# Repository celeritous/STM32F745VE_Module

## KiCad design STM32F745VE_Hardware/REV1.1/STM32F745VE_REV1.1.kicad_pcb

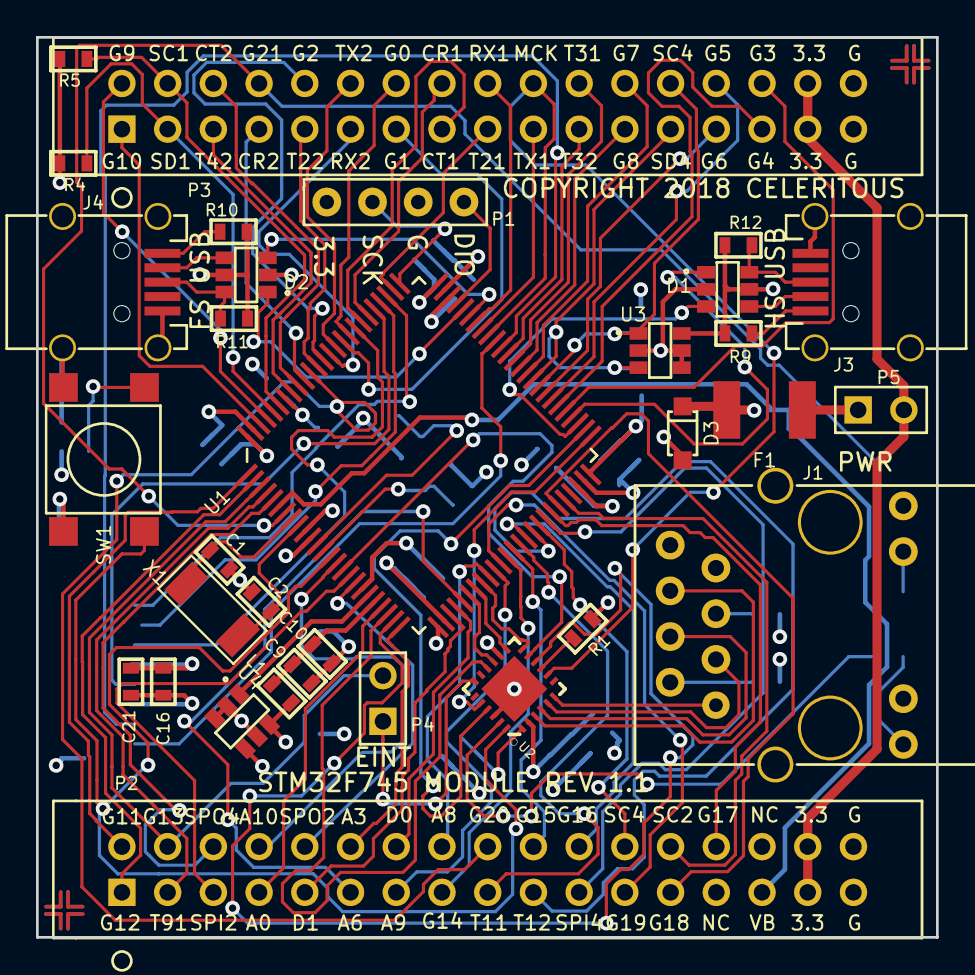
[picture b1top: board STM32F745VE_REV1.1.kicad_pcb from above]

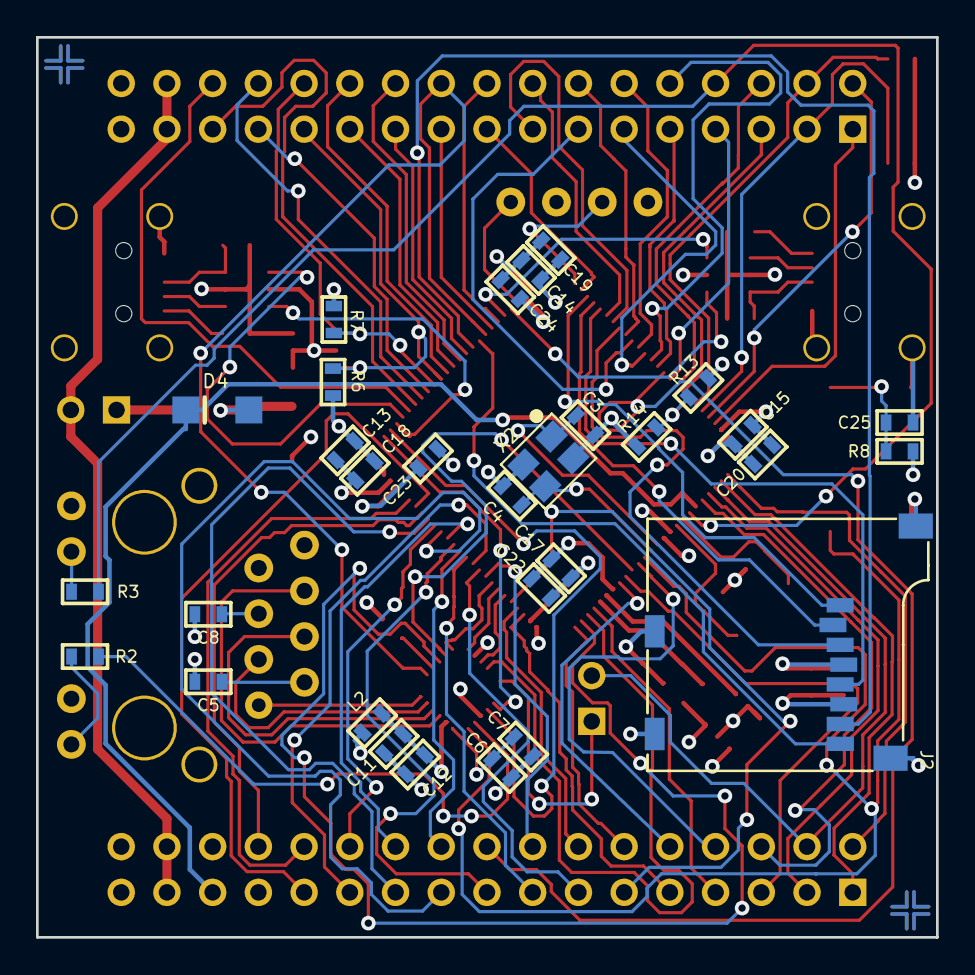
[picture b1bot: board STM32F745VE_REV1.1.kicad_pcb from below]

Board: 4 copper layers, 50.0 x 50.0 mm, 66 parts (30 on the bottom side), 112 nets.

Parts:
C1, C2, C3, C4: 12pF; P0603
C5, C6, C8, C9, C11, C13, C14, C15, C16, C17: 0.10uF; P0603
C7, C23, C24: 2.2uF; P0603
C10, C12, C18, C19, C20, C21, C22: 10.0uF; P0603
C25: 0.010uF; P0603
D1, D2: USBLC6-2; SOT23-6
D3: SMP3V3; SOD123
D4: D_Small; MINI_SMA
F1: FUSE_PTC_.75A_33V; P1812
J1: CONNECTOR_RJ45_SI-60062; CONNECTOR_ETHERNET_SI60062
J2: SOCKET_MICRO_SD_SMT_3M; CONN_SDMICRO_3M
J3, J4: USB_MINI_B_SMD; CONN_USB_UX60-MB
L1, L2: FERRITE_BEAD; P0603
P1: CONN_1x4; Connector_1x4_100mil_TH
P2, P3: Header_2x17; Header_2x17_Shrouded_100mil
P4, P5: Header_2x1; Header_2x1_Shrouded_100mil
R1: 6.49kΩ; P0603
R2, R3: 220.0Ω; P0603
R4, R5, R6, R7, R8, R14: 4.70kΩ; P0603
R9, R10, R13: ZERO_Ω; P0603
R11, R12: 1.50kΩ; P0603
REF01, REF04: FIDUCIAL_BOTTOM
REF02, REF03: FIDUCIAL_TOP
SW1: PUSHBUTTON_SPST_6MM_SMD; SWITCH_6MM_PB
U1: STM32F745VE; QFP_100_14X14_0.5
U2: KSZ8081RNA; QFN24_4X4mm_0.5mm_PWR
U3: 24AA02E64OT; SOT23-6
U4: MCP1501-30; SOT23-6
X1: ABS10-32.768kHz; XTAL_1.8X4.9mm
X2: ABM8G-12.00MHz; XTAL_3.2X2.5

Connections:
+3.3V: C13.1, C14.1, C15.1, C16.1, C17.1, C18.1, C19.1, C20.1, C21.1, C22.1, D1.5, D2.5, D3.K, D4.A, F1.1, J1.10, J1.12, J2.4, L1.1, L2.1, P1.4, R4.2, R5.2, R6.2, R7.2, R8.1, R9.1, R10.1, R11.1, R12.2, R13.1, U1.11, U1.27, U1.50, U1.75, U1.100, U2.14, U3.6, U4.4, U4.6
/+3.0VREF: U1.20, U4.1
/+3.3VANA: C9.1, C10.1, L1.2, U1.21
/+3.3VETH: C11.1, C12.1, L2.2, U2.2
/+3.3VEXT: P2.31, P2.32, P3.31, P3.32, P5.2
/ADC_0: P2.7, U1.22
/ADC_3: P2.12, U1.25
/ADC_6: P2.11, U1.30
/ADC_8: P2.16, U1.34
/ADC_9: P2.13, U1.35
/ADC_10: P2.8, U1.15
/BOOT0: R13.2, R14.1, U1.94
/CAN1_RX: P3.16, U1.81
/CAN1_TX: P3.15, U1.82
/CAN2_RX: P3.7, U1.91
/CAN2_TX: P3.6, U1.92
/DAC_0: P2.14, U1.29
/DAC_1: P2.9, U1.28
/ETH_CRS_DV: U1.31, U2.15
/ETH_INT: P4.1, U2.18
/ETH_LED: R2.1, U2.23
/ETH_MDC: U1.16, U2.11
/ETH_MDIO: U1.24, U2.10
/ETH_REF_CLK: U1.23, U2.16
/ETH_RXC: C8.1, J1.5
/ETH_RXD0: U1.32, U2.13
/ETH_RXD1: U1.33, U2.12
/ETH_RXM: J1.6, U2.3
/ETH_RXP: J1.4, U2.4
/ETH_TXC: C5.1, J1.2
/ETH_TXD0: U1.51, U2.20
/ETH_TXD1: U1.52, U2.21
/ETH_TXM: J1.3, U2.5
/ETH_TXP: J1.1, U2.6
/GPIO_0: P3.14, U1.84
/GPIO_1: P3.13, U1.85
/GPIO_2: P3.10, U1.88
/GPIO_3: P3.30, U1.55
/GPIO_4: P3.29, U1.56
/GPIO_5: P3.28, U1.57
/GPIO_6: P3.27, U1.58
/GPIO_7: P3.24, U1.61
/GPIO_8: P3.23, U1.62
/GPIO_9: P3.2, U1.97
/GPIO_10: P3.1, U1.98
/GPIO_11: P2.2, U1.1
/GPIO_12: P2.1, U1.2
/GPIO_13: P2.4, P4.2, U1.3
/GPIO_14: P2.15, U1.37
/GPIO_15: P2.20, U1.38
/GPIO_16: P2.22, U1.40
/GPIO_17: P2.28, U1.44
/GPIO_18: P2.25, U1.45
/GPIO_19: P2.23, U1.36
/GPIO_20: P2.18, U1.90
/GPIO_21: P3.8, R3.1, U1.7
/I2C1_SCL: P3.4, R5.1, U1.95
/I2C1_SDA: P3.3, R4.1, U1.96
/I2C4_SCL: P3.26, R7.1, U1.59, U3.1
/I2C4_SDA: P3.25, R6.1, U1.60, U3.3
/JTAG_SWCLK: P1.3, U1.76
/JTAG_SWDIO: P1.1, U1.72
/MCLKOUT: P3.20, U1.67, U2.8
/MCU_RST: SW1.2, U1.14, U2.24
/OSC32IN: C1.1, U1.8, X1.1
/OSC32OUT: C2.1, U1.9, X1.2
/OSCHSIN: C3.1, U1.12, X2.1
/OSCHSOUT: C4.1, U1.13, X2.3
/SDMMC_CK: J2.5, U1.80
/SDMMC_CMD: J2.3, U1.83
/SDMMC_D0: J2.7, U1.65
/SDMMC_D1: J2.8, U1.66
/SDMMC_D2: J2.1, U1.78
/SDMMC_D3: J2.2, U1.79
/SPI2_MISO: P2.5, U1.17
/SPI2_MOSI: P2.10, U1.18
/SPI2_SCK: P2.26, U1.46
/SPI4_MISO: P2.21, U1.43
/SPI4_MOSI: P2.6, U1.5
/SPI4_SCK: P2.24, U1.42
/TIM1_CH1: P2.17, U1.39
/TIM1_CH2: P2.19, U1.41
/TIM2_CH1: P3.17, U1.77
/TIM2_CH2: P3.9, U1.89
/TIM3_CH1: P3.22, U1.63
/TIM3_CH2: P3.21, U1.64
/TIM4_CH2: P3.5, U1.93
/TIM9_CH1: P2.3, U1.4
/USART1_RX: P3.18, U1.69
/USART1_TX: P3.19, U1.68
/USART2_RX: P3.11, U1.87
/USART2_TX: P3.12, U1.86
/USB_FS_DM: D2.3, U1.70
/USB_FS_DP: D2.1, U1.71
/USB_HS_DM: D1.3, U1.53
/USB_HS_DP: D1.1, U1.54
/VBATT: D4.K, P2.29, U1.6
/VCAP1: C23.1, U1.48
/VCAP2: C24.1, U1.73
GND: C1.2, C2.2, C3.2, C4.2, C5.2, C6.2, C7.2, C8.2, C9.2, C10.2, C11.2, C12.2, C13.2, C14.2, C15.2, C16.2, C17.2, C18.2, C19.2, C20.2, C21.2, C22.2, C23.2, C24.2, C25.2, D1.2, D2.2, D3.A, J1.8, J2.6, J2.9, J2.10, J2.11, J2.12, J3.5, J3.6, J3.7, J3.8, J3.9, J4.5, J4.6, J4.7, J4.8, J4.9, P1.2, P2.33, P2.34, P3.33, P3.34, R1.1, R14.2, SW1.3, SW1.4, U1.10, U1.19, U1.26, U1.49, U1.74, U1.99, U2.22, U2.25, U3.2, U3.4, U3.5, U4.2, U4.3, U4.5, X2.2, X2.4
unnamed: C6.1, C7.1, U2.1
unnamed: C25.1, R8.2, SW1.1
unnamed: D1.4, J3.2
unnamed: D1.6, J3.3, R12.1
unnamed: D2.4, J4.2
unnamed: D2.6, J4.3, R11.2
unnamed: F1.2, P5.1
unnamed: J1.9, R2.2
unnamed: J1.11, R3.2
unnamed: J3.1, R9.2
unnamed: J4.1, R10.2
unnamed: R1.2, U2.9

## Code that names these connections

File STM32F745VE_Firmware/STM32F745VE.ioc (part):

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Mcu.Name=STM32F745V(E-G)Tx
Mcu.Package=LQFP100
Mcu.UserName=STM32F745VETx
PA0/WKUP.Signal=ADCx_IN0
PA1.Mode=RMII
PA1.Signal=ETH_REF_CLK
PA10.Mode=Asynchronous
PA10.Signal=USART1_RX
PA11.Mode=Device_Only
PA11.Signal=USB_OTG_FS_DM
PA12.Mode=Device_Only
PA12.Signal=USB_OTG_FS_DP
PA13.Mode=Serial_Wire
PA13.Signal=SYS_JTMS-SWDIO
PA14.Mode=Serial_Wire
PA14.Signal=SYS_JTCK-SWCLK
PA15.Signal=S_TIM2_CH1_ETR
PA2.Mode=RMII
PA2.Signal=ETH_MDIO
PA3.Signal=ADCx_IN3
PA4.Signal=COMP_DAC1_group
PA5.Signal=COMP_DAC2_group
PA6.Signal=ADCx_IN6
PA7.Mode=RMII
PA7.Signal=ETH_CRS_DV
PA8.Mode=Clock-out-1
PA8.Signal=RCC_MCO_1
PA9.Mode=Asynchronous
PA9.Signal=USART1_TX
PB0.Signal=ADCx_IN8
PB1.Signal=ADCx_IN9
PB10.Mode=Full_Duplex_Master
PB10.Signal=SPI2_SCK
PB11.Mode=RMII
PB11.Signal=ETH_TX_EN
PB12.Mode=RMII
PB12.Signal=ETH_TXD0
PB13.Mode=RMII
PB13.Signal=ETH_TXD1
PB14.Mode=Host_FS
PB14.Signal=USB_OTG_HS_DM
PB15.Mode=Host_FS
PB15.Signal=USB_OTG_HS_DP
PB2.GPIOParameters=GPIO_Label
PB2.GPIO_Label=GPIO_20
PB2.Signal=GPIO_Input
PB3.Signal=S_TIM2_CH2
PB4.GPIOParameters=GPIO_Label
PB4.GPIO_Label=GPIO_21
PB4.Signal=GPIO_Input
PB5.Mode=Slave
PB5.Signal=CAN2_RX
PB6.Mode=Slave
PB6.Signal=CAN2_TX
PB7.Signal=S_TIM4_CH2
PB8.Mode=I2C
PB8.Signal=I2C1_SCL
PB9.Mode=I2C
PB9.Signal=I2C1_SDA
PC0.Signal=ADCx_IN10
PC1.Mode=RMII
PC1.Signal=ETH_MDC
PC10.Mode=SD_4_bits_Wide_bus
PC10.Signal=SDMMC1_D2
PC11.Mode=SD_4_bits_Wide_bus
PC11.Signal=SDMMC1_D3
PC12.Mode=SD_4_bits_Wide_bus
PC12.Signal=SDMMC1_CK
PC13.GPIOParameters=GPIO_Label
PC13.GPIO_Label=GPIO_22
PC13.Signal=GPIO_Input
PC14/OSC32_IN.Mode=LSE-External-Oscillator
PC14/OSC32_IN.Signal=RCC_OSC32_IN
PC15/OSC32_OUT.Mode=LSE-External-Oscillator
PC15/OSC32_OUT.Signal=RCC_OSC32_OUT
PC2.Mode=Full_Duplex_Master
PC2.Signal=SPI2_MISO
PC3.Mode=Full_Duplex_Master
PC3.Signal=SPI2_MOSI
PC4.Mode=RMII
PC4.Signal=ETH_RXD0
PC5.Mode=RMII
PC5.Signal=ETH_RXD1
PC6.Signal=S_TIM3_CH1
PC7.Signal=S_TIM3_CH2
PC8.Mode=SD_4_bits_Wide_bus
PC8.Signal=SDMMC1_D0
PC9.Mode=SD_4_bits_Wide_bus
PC9.Signal=SDMMC1_D1
PD0.Mode=Master
PD0.Signal=CAN1_RX
PD1.Mode=Master
PD1.Signal=CAN1_TX
PD10.GPIOParameters=GPIO_Label
PD10.GPIO_Label=GPIO_5
PD10.Signal=GPIO_Input
PD11.GPIOParameters=GPIO_Label
PD11.GPIO_Label=GPIO_6
PD11.Signal=GPIO_Input
PD12.Mode=I2C
PD12.Signal=I2C4_SCL
PD13.Mode=I2C
PD13.Signal=I2C4_SDA
PD14.GPIOParameters=GPIO_Label
PD14.GPIO_Label=GPIO_7
PD14.Signal=GPIO_Input
PD15.GPIOParameters=GPIO_Label
PD15.GPIO_Label=GPIO_8
PD15.Signal=GPIO_Input
PD2.Mode=SD_4_bits_Wide_bus
PD2.Signal=SDMMC1_CMD
PD3.GPIOParameters=GPIO_Label
PD3.GPIO_Label=GPIO_0
PD3.Signal=GPIO_Input
PD4.GPIOParameters=GPIO_Label
PD4.GPIO_Label=GPIO_1
PD4.Signal=GPIO_Input
PD5.Mode=Asynchronous
PD5.Signal=USART2_TX
PD6.Mode=Asynchronous
PD6.Signal=USART2_RX
PD7.GPIOParameters=GPIO_Label
PD7.GPIO_Label=GPIO_2
PD7.Signal=GPIO_Input
PD8.GPIOParameters=GPIO_Label
PD8.GPIO_Label=GPIO_3
PD8.Signal=GPIO_Input
PD9.GPIOParameters=GPIO_Label
PD9.GPIO_Label=GPIO_4
PD9.Signal=GPIO_Input
PE0.GPIOParameters=GPIO_Label
PE0.GPIO_Label=GPIO_9
PE0.Signal=GPIO_Input
PE1.GPIOParameters=GPIO_Label
PE1.GPIO_Label=GPIO_10
PE1.Signal=GPIO_Input
PE10.GPIOParameters=GPIO_Label
PE10.GPIO_Label=GPIO_16
PE10.Signal=GPIO_Input
PE11.Signal=S_TIM1_CH2
PE12.GPIOParameters=GPIO_Label
PE12.GPIO_Label=GPIO_17
PE12.Mode=Full_Duplex_Master
PE12.Signal=SPI4_SCK
PE13.Mode=Full_Duplex_Master
PE13.Signal=SPI4_MISO
PE14.GPIOParameters=GPIO_Label
PE14.GPIO_Label=GPIO_18
PE14.Signal=GPIO_Input
PE15.GPIOParameters=GPIO_Label
PE15.GPIO_Label=GPIO_19
PE15.Signal=GPIO_Input
PE2.GPIOParameters=GPIO_Label
PE2.GPIO_Label=GPIO_11
PE2.Signal=GPIO_Input
PE3.GPIOParameters=GPIO_Label
PE3.GPIO_Label=GPIO_12
PE3.Signal=GPIO_Input
PE4.GPIOParameters=GPIO_Label
PE4.GPIO_Label=GPIO_13
PE4.Signal=GPIO_Input
PE5.Signal=S_TIM9_CH1
PE6.Mode=Full_Duplex_Master
PE6.Signal=SPI4_MOSI
PE7.GPIOParameters=GPIO_Label
PE7.GPIO_Label=GPIO_14
PE7.Signal=GPIO_Input
PE8.GPIOParameters=GPIO_Label
PE8.GPIO_Label=GPIO_15
PE8.Signal=GPIO_Input
PE9.Signal=S_TIM1_CH1
PH0/OSC_IN.Mode=HSE-External-Oscillator
PH0/OSC_IN.Signal=RCC_OSC_IN
PH1/OSC_OUT.Mode=HSE-External-Oscillator
PH1/OSC_OUT.Signal=RCC_OSC_OUT
RCC.HSE_VALUE=12000000
RCC.SYSCLKFreq_VALUE=100000000
RCC.SYSCLKSource=RCC_SYSCLKSOURCE_PLLCLK

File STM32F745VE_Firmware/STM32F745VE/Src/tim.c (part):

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    __HAL_RCC_TIM1_CLK_ENABLE();
  
    /**TIM1 GPIO Configuration    
    PE9     ------> TIM1_CH1
    PE11     ------> TIM1_CH2 
    */
    GPIO_InitStruct.Pin = GPIO_PIN_9|GPIO_PIN_11;
    GPIO_InitStruct.Mode = GPIO_MODE_AF_PP;
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    __HAL_RCC_TIM2_CLK_ENABLE();
  
    /**TIM2 GPIO Configuration    
    PA15     ------> TIM2_CH1
    PB3     ------> TIM2_CH2 
    */
    GPIO_InitStruct.Pin = GPIO_PIN_15;
    GPIO_InitStruct.Mode = GPIO_MODE_AF_PP;
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    __HAL_RCC_TIM3_CLK_ENABLE();
  
    /**TIM3 GPIO Configuration    
    PC6     ------> TIM3_CH1
    PC7     ------> TIM3_CH2 
    */
    GPIO_InitStruct.Pin = GPIO_PIN_6|GPIO_PIN_7;
    GPIO_InitStruct.Mode = GPIO_MODE_AF_PP;
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
  /* USER CODE END TIM4_MspPostInit 0 */
    /**TIM4 GPIO Configuration    
    PB7     ------> TIM4_CH2 
    */
    GPIO_InitStruct.Pin = GPIO_PIN_7;
    GPIO_InitStruct.Mode = GPIO_MODE_AF_PP;
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  /* USER CODE END TIM9_MspPostInit 0 */
  
    /**TIM9 GPIO Configuration    
    PE5     ------> TIM9_CH1 
    */
    GPIO_InitStruct.Pin = GPIO_PIN_5;
    GPIO_InitStruct.Mode = GPIO_MODE_AF_PP;
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    __HAL_RCC_TIM1_CLK_DISABLE();
  
    /**TIM1 GPIO Configuration    
    PE9     ------> TIM1_CH1
    PE11     ------> TIM1_CH2 
    */
    HAL_GPIO_DeInit(GPIOE, GPIO_PIN_9|GPIO_PIN_11);

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    __HAL_RCC_TIM2_CLK_DISABLE();
  
    /**TIM2 GPIO Configuration    
    PA15     ------> TIM2_CH1
    PB3     ------> TIM2_CH2 
    */
    HAL_GPIO_DeInit(GPIOA, GPIO_PIN_15);

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    __HAL_RCC_TIM3_CLK_DISABLE();
  
    /**TIM3 GPIO Configuration    
    PC6     ------> TIM3_CH1
    PC7     ------> TIM3_CH2 
    */
    HAL_GPIO_DeInit(GPIOC, GPIO_PIN_6|GPIO_PIN_7);

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
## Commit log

2018-03-07 STM32F745VE KiCAD Initial coomit
    STM32F745VE KiCAD Initial coomit
2018-03-07 Commit with TrueStudio & Cube project
2018-04-19 Rev 1.1 update

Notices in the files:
STM32F745VE_Firmware/STM32F745VE/Src/tim.c:
Copyright (c) 2018 STMicroelectronics International N.V.
All rights reserved.
(C) COPYRIGHT STMicroelectronics *****END OF FILE
STM32F745VE_Hardware/REV1.1/STM32F745VE_REV1.1.kicad_pcb:
COPYRIGHT 2018 CELERITOUS
